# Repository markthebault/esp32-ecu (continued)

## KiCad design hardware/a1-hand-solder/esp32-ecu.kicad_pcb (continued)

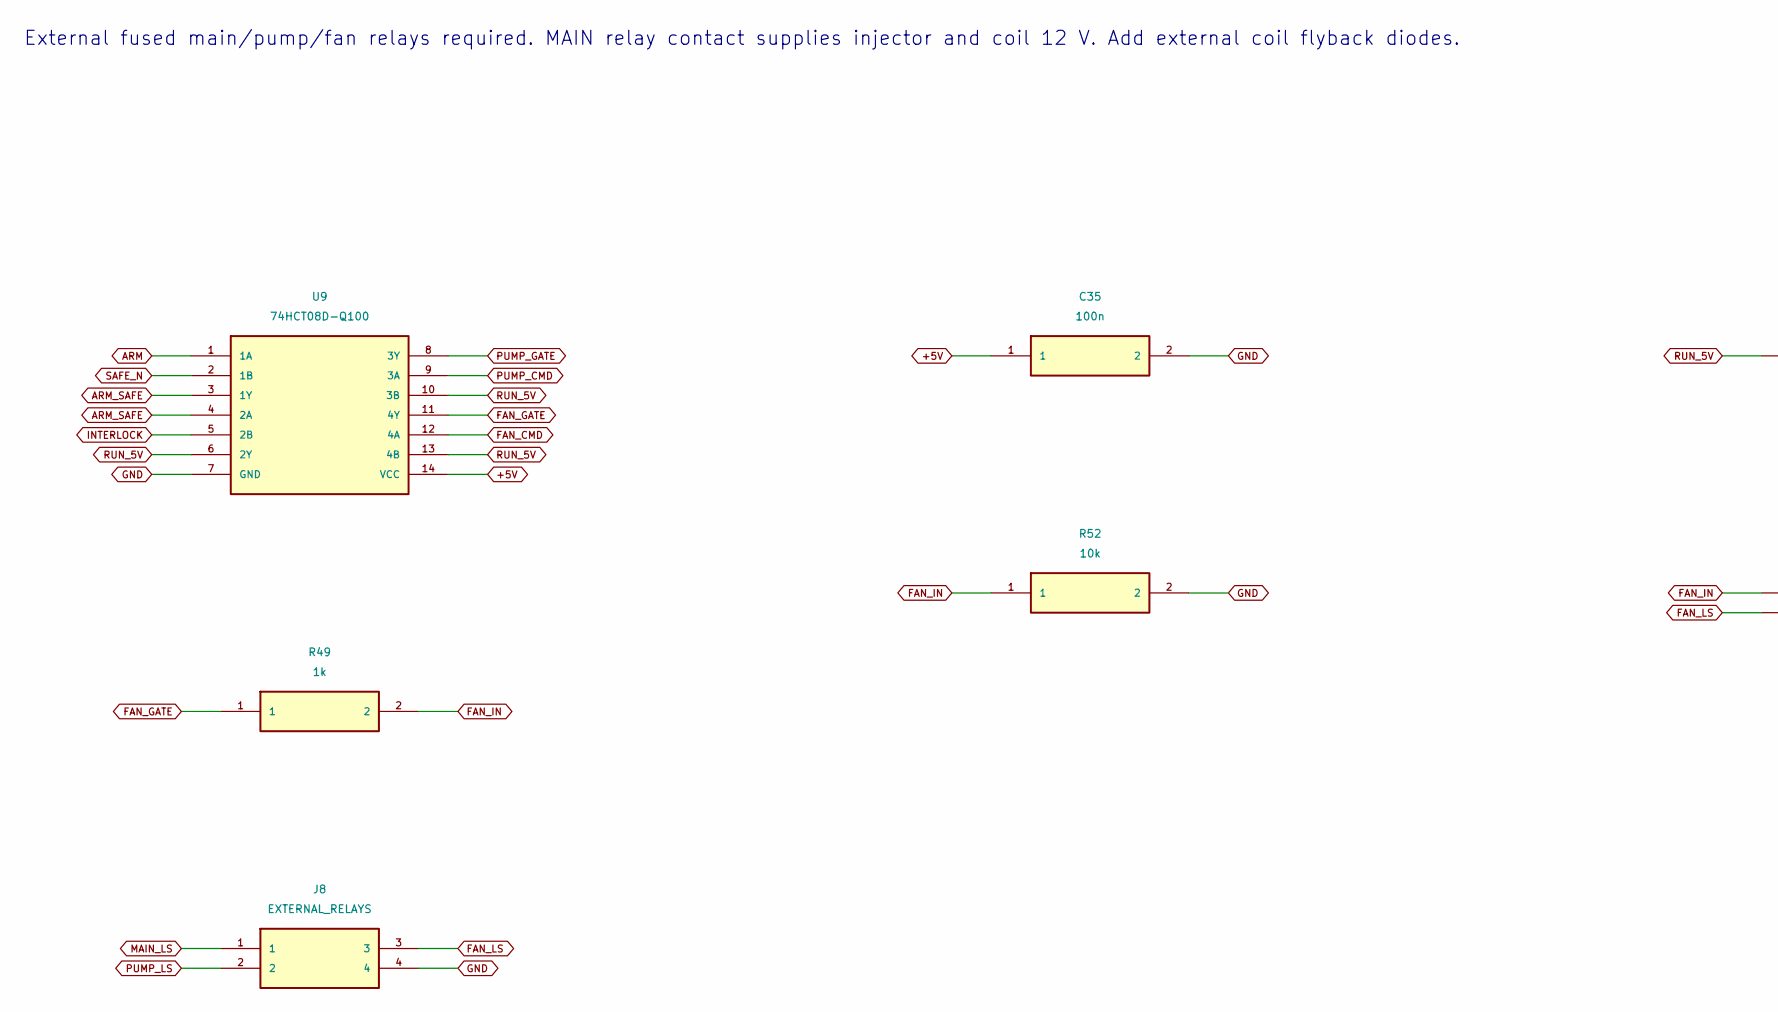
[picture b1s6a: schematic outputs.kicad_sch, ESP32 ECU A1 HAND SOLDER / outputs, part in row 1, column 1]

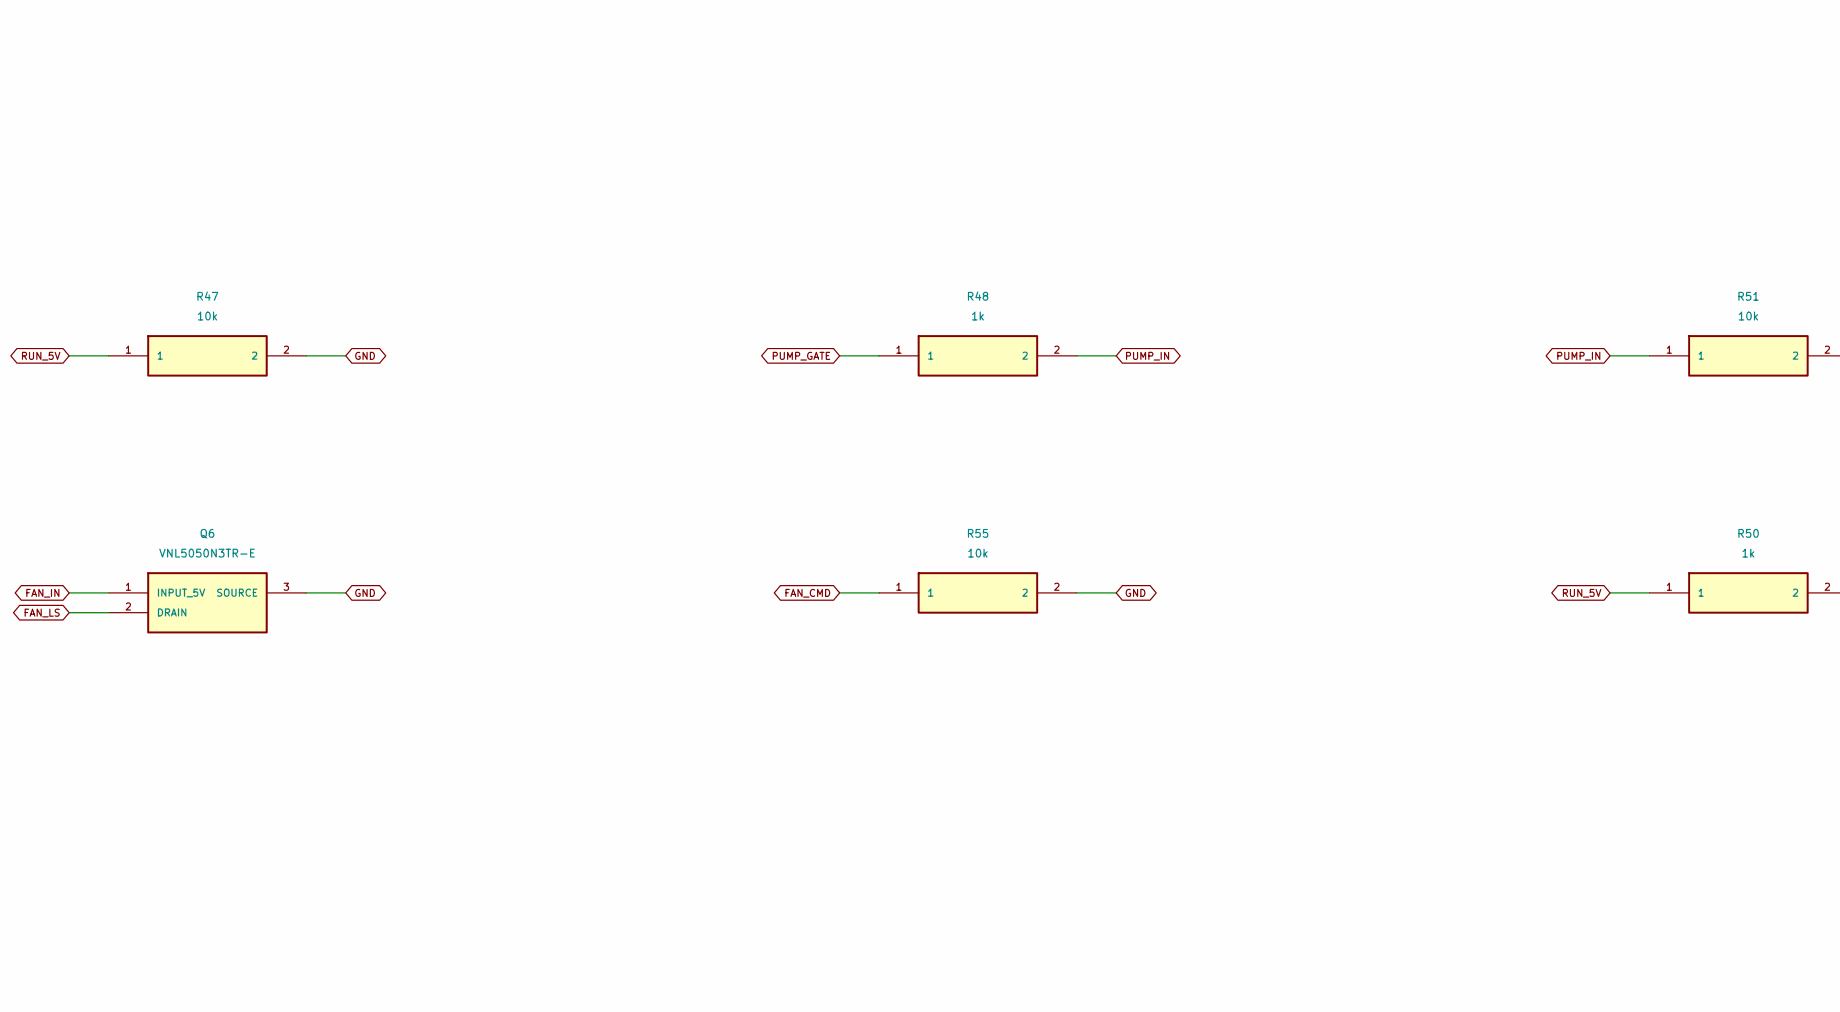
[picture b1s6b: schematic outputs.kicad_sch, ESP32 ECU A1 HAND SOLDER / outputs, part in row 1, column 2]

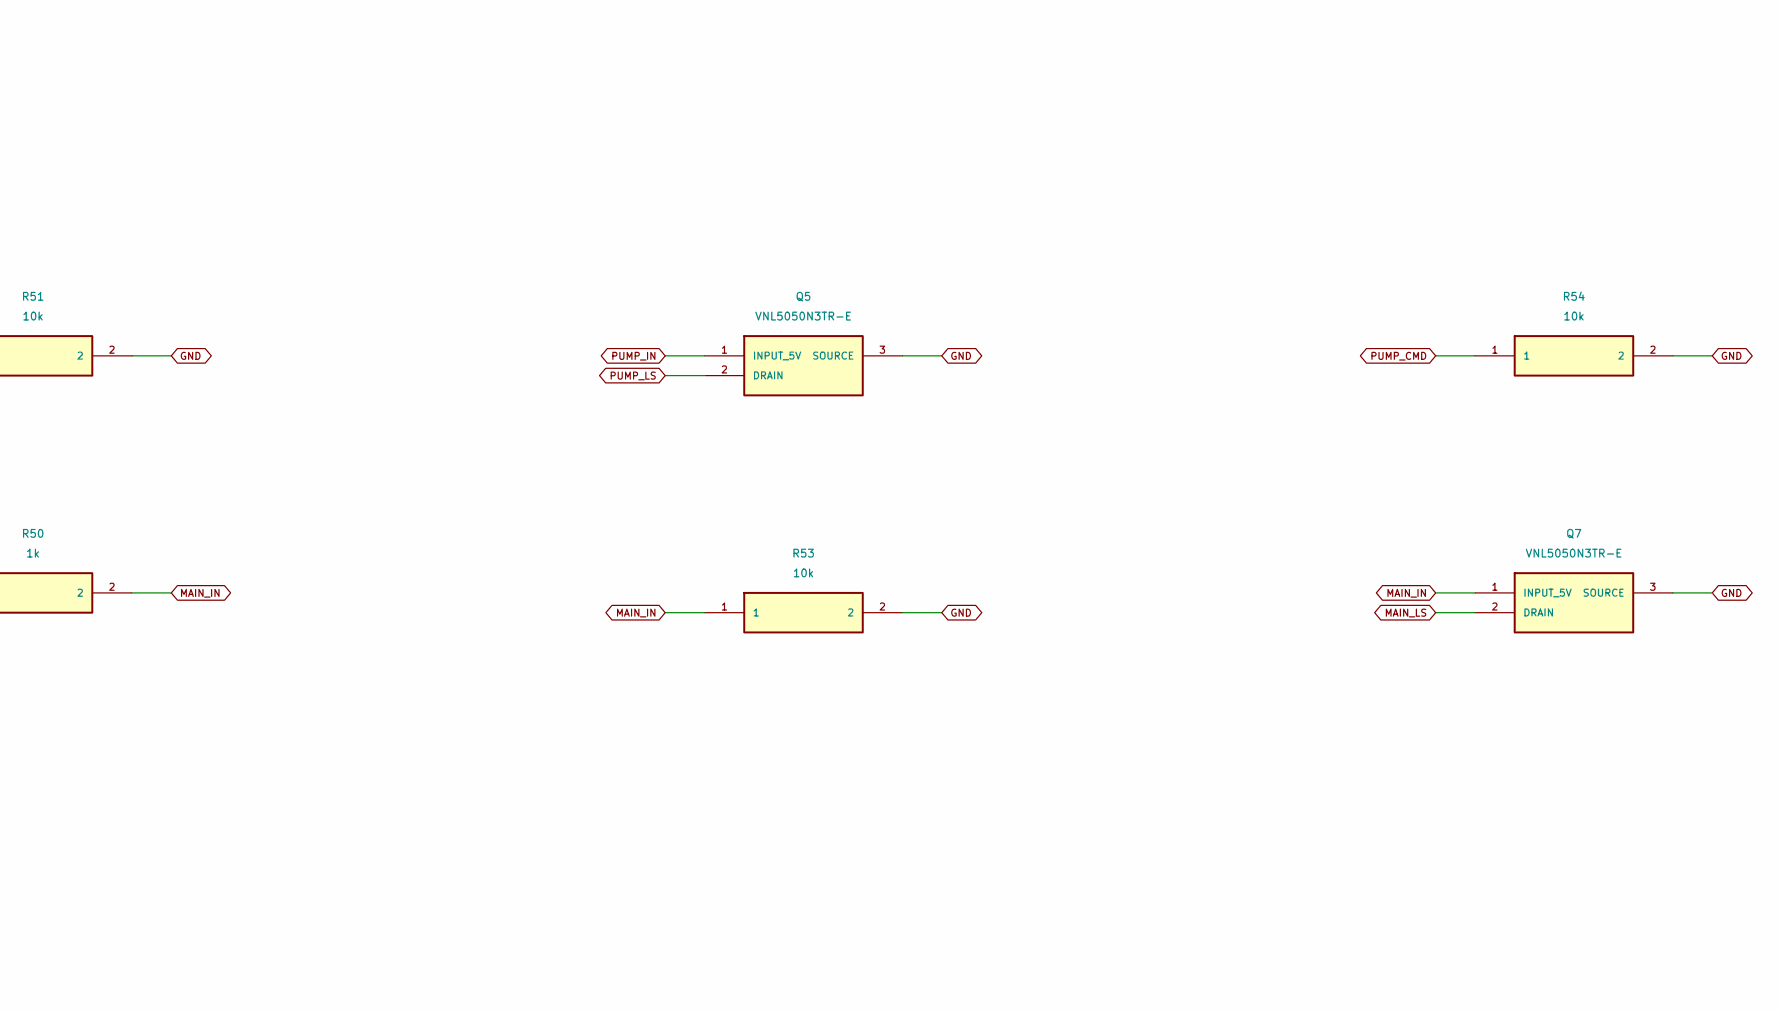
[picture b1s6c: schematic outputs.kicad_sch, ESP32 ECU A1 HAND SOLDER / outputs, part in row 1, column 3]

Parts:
C35: 100n; C_1206_3216Metric_Pad1.33x1.80mm_HandSolder
J8: EXTERNAL_RELAYS; JST_VH_B4P-VH_1x04_P3.96mm_Vertical; MPN B4P-VH(LF)(SN)
Q5, Q6, Q7: VNL5050N3TR-E; SOT-223-3_TabPin2; MPN VNL5050N3TR-E
R47, R51, R52, R53, R54, R55: 10k; R_1206_3216Metric_Pad1.30x1.75mm_HandSolder
R48, R49, R50: 1k; R_1206_3216Metric_Pad1.30x1.75mm_HandSolder
U9: 74HCT08D-Q100; SOIC-14_3.9x8.7mm_P1.27mm; MPN 74HCT08D-Q100,118

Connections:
+5V: C35.1, U9.14 (VCC); also elsewhere on the board
ARM: U9.1 (1A); also elsewhere on the board
ARM_SAFE: U9.3 (1Y), U9.4 (2A)
FAN_CMD: R55.1, U9.12 (4A); also elsewhere on the board
FAN_GATE: R49.1, U9.11 (4Y)
FAN_IN: Q6.1 (INPUT_5V), R49.2, R52.1
FAN_LS: J8.3, Q6.2 (DRAIN)
GND: C35.2, J8.4, Q5.3 (SOURCE), Q6.3 (SOURCE), Q7.3 (SOURCE), R47.2, R51.2, R52.2, R53.2, R54.2, R55.2, U9.7 (GND); also elsewhere on the board
INTERLOCK: U9.5 (2B); also elsewhere on the board
MAIN_IN: Q7.1 (INPUT_5V), R50.2, R53.1
MAIN_LS: J8.1, Q7.2 (DRAIN)
PUMP_CMD: R54.1, U9.9 (3A); also elsewhere on the board
PUMP_GATE: R48.1, U9.8 (3Y)
PUMP_IN: Q5.1 (INPUT_5V), R48.2, R51.1
PUMP_LS: J8.2, Q5.2 (DRAIN)
RUN_5V: R47.1, R50.1, U9.6 (2Y), U9.10 (3B), U9.13 (4B); also elsewhere on the board
SAFE_N: U9.2 (1B); also elsewhere on the board

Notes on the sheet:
External fused main/pump/fan relays required. MAIN relay contact supplies injector and coil 12 V. Add external coil flyback diodes.

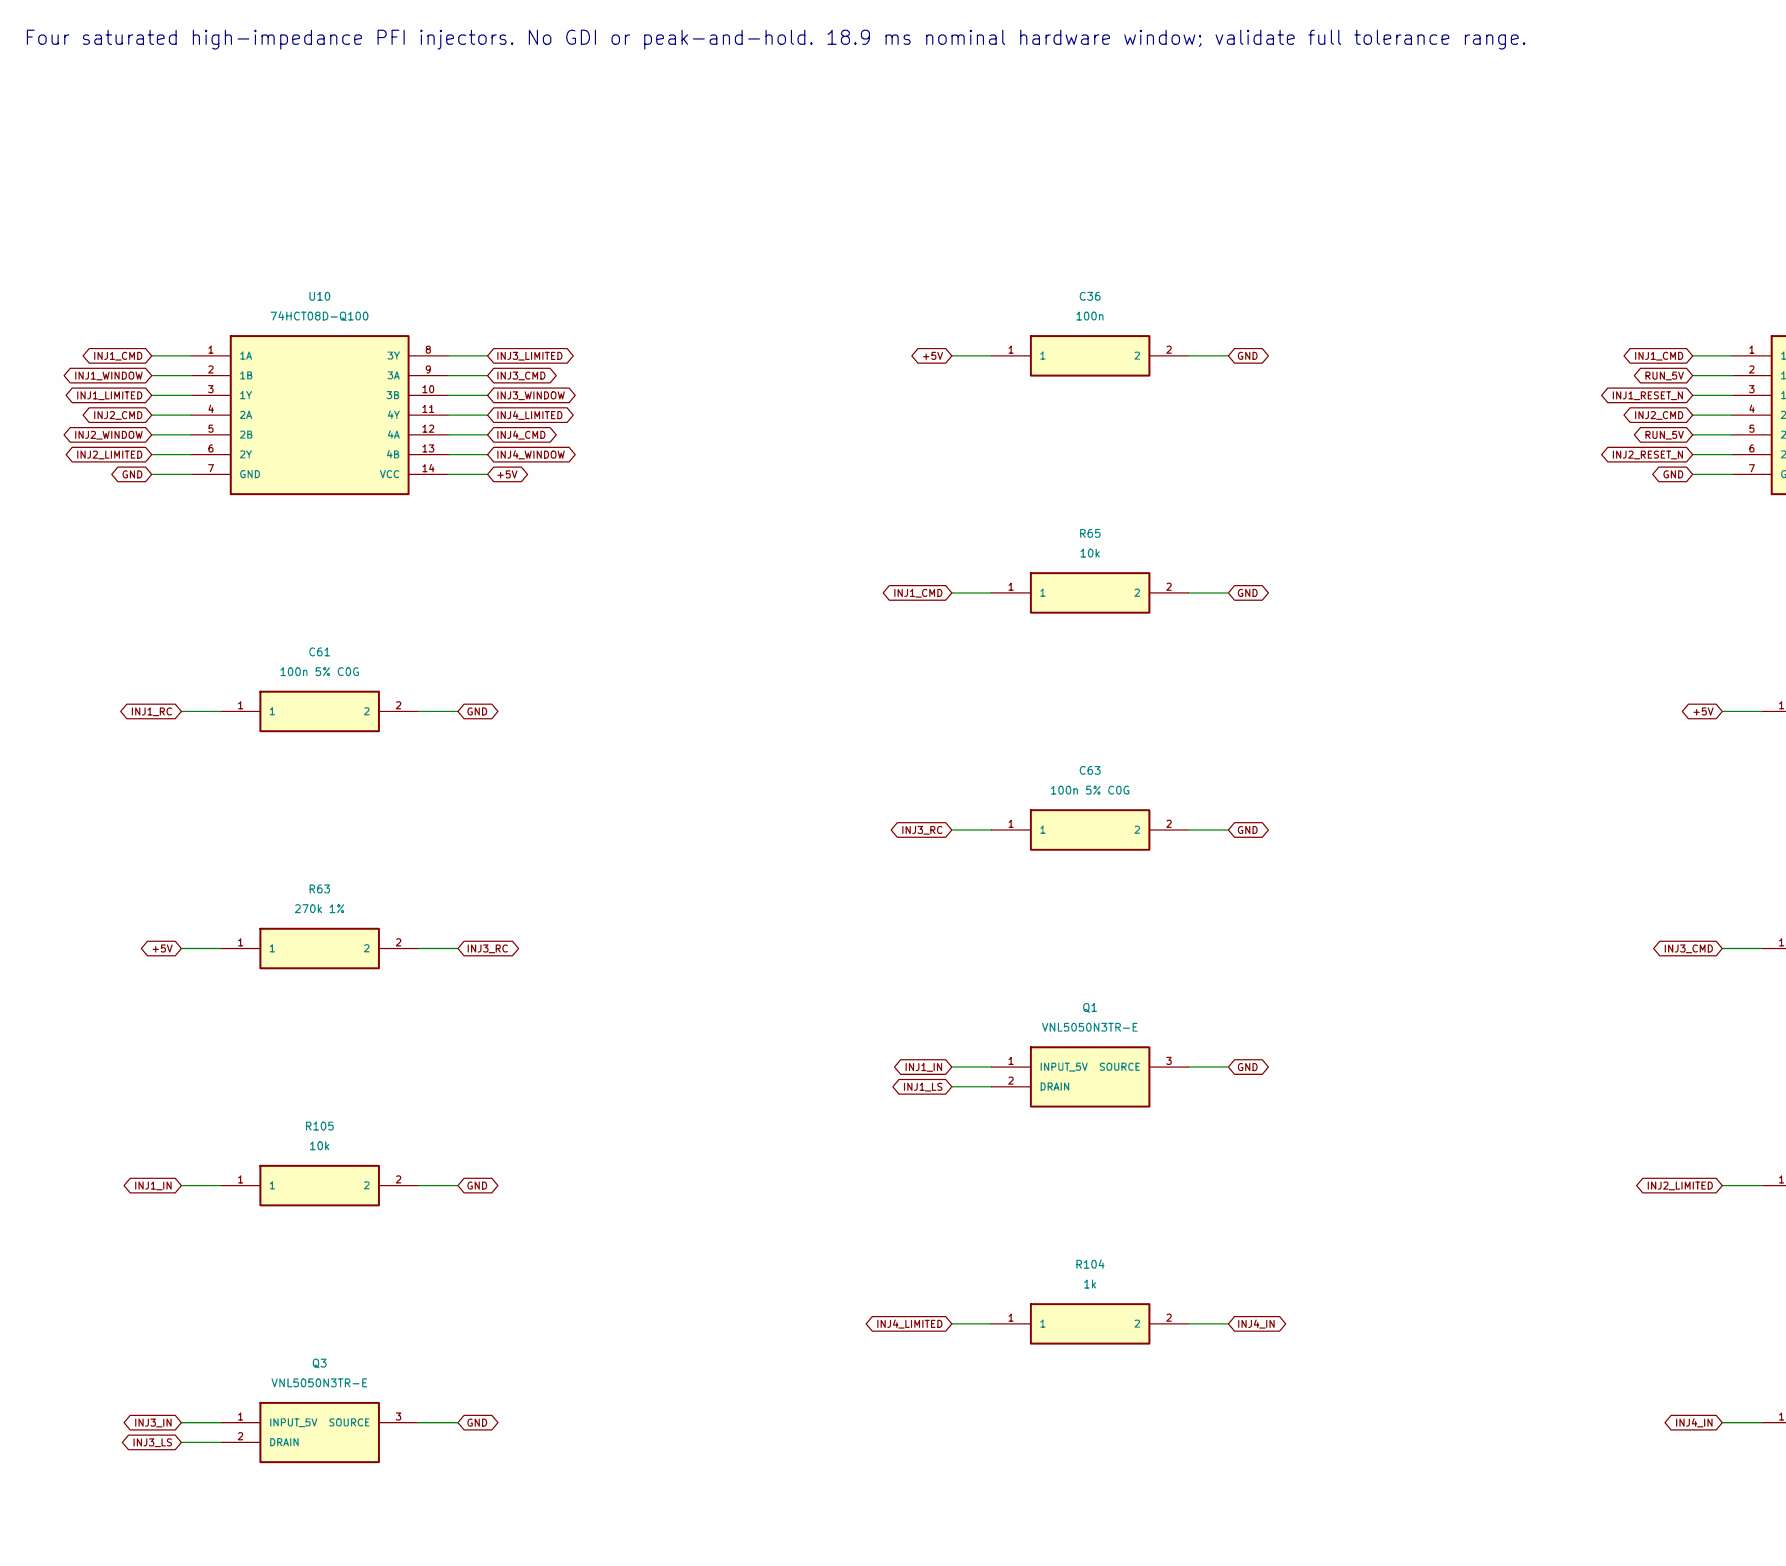
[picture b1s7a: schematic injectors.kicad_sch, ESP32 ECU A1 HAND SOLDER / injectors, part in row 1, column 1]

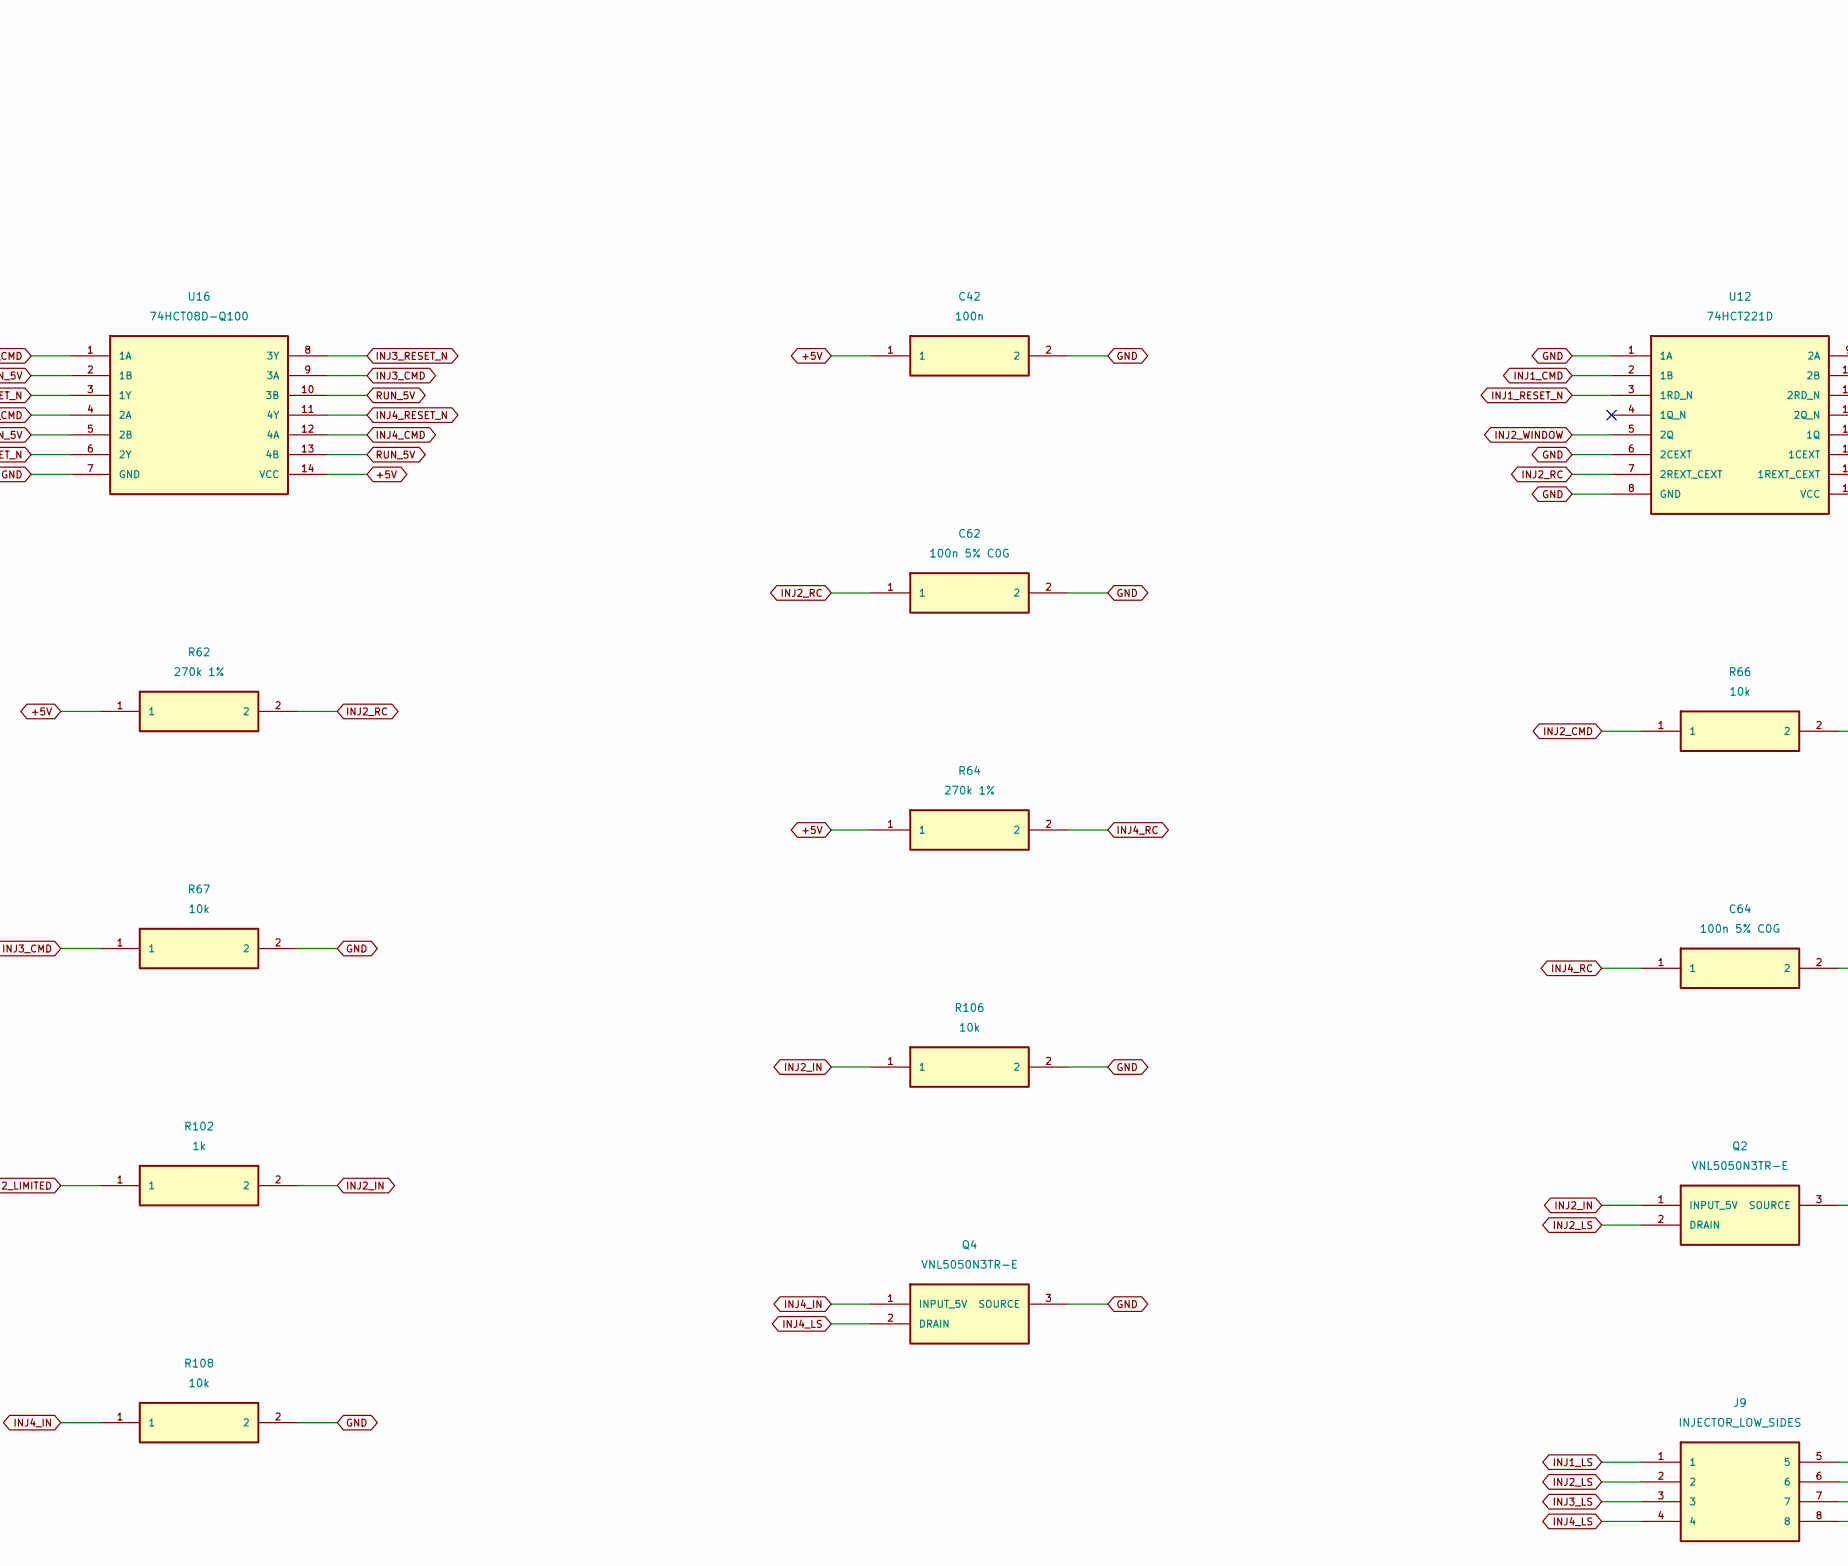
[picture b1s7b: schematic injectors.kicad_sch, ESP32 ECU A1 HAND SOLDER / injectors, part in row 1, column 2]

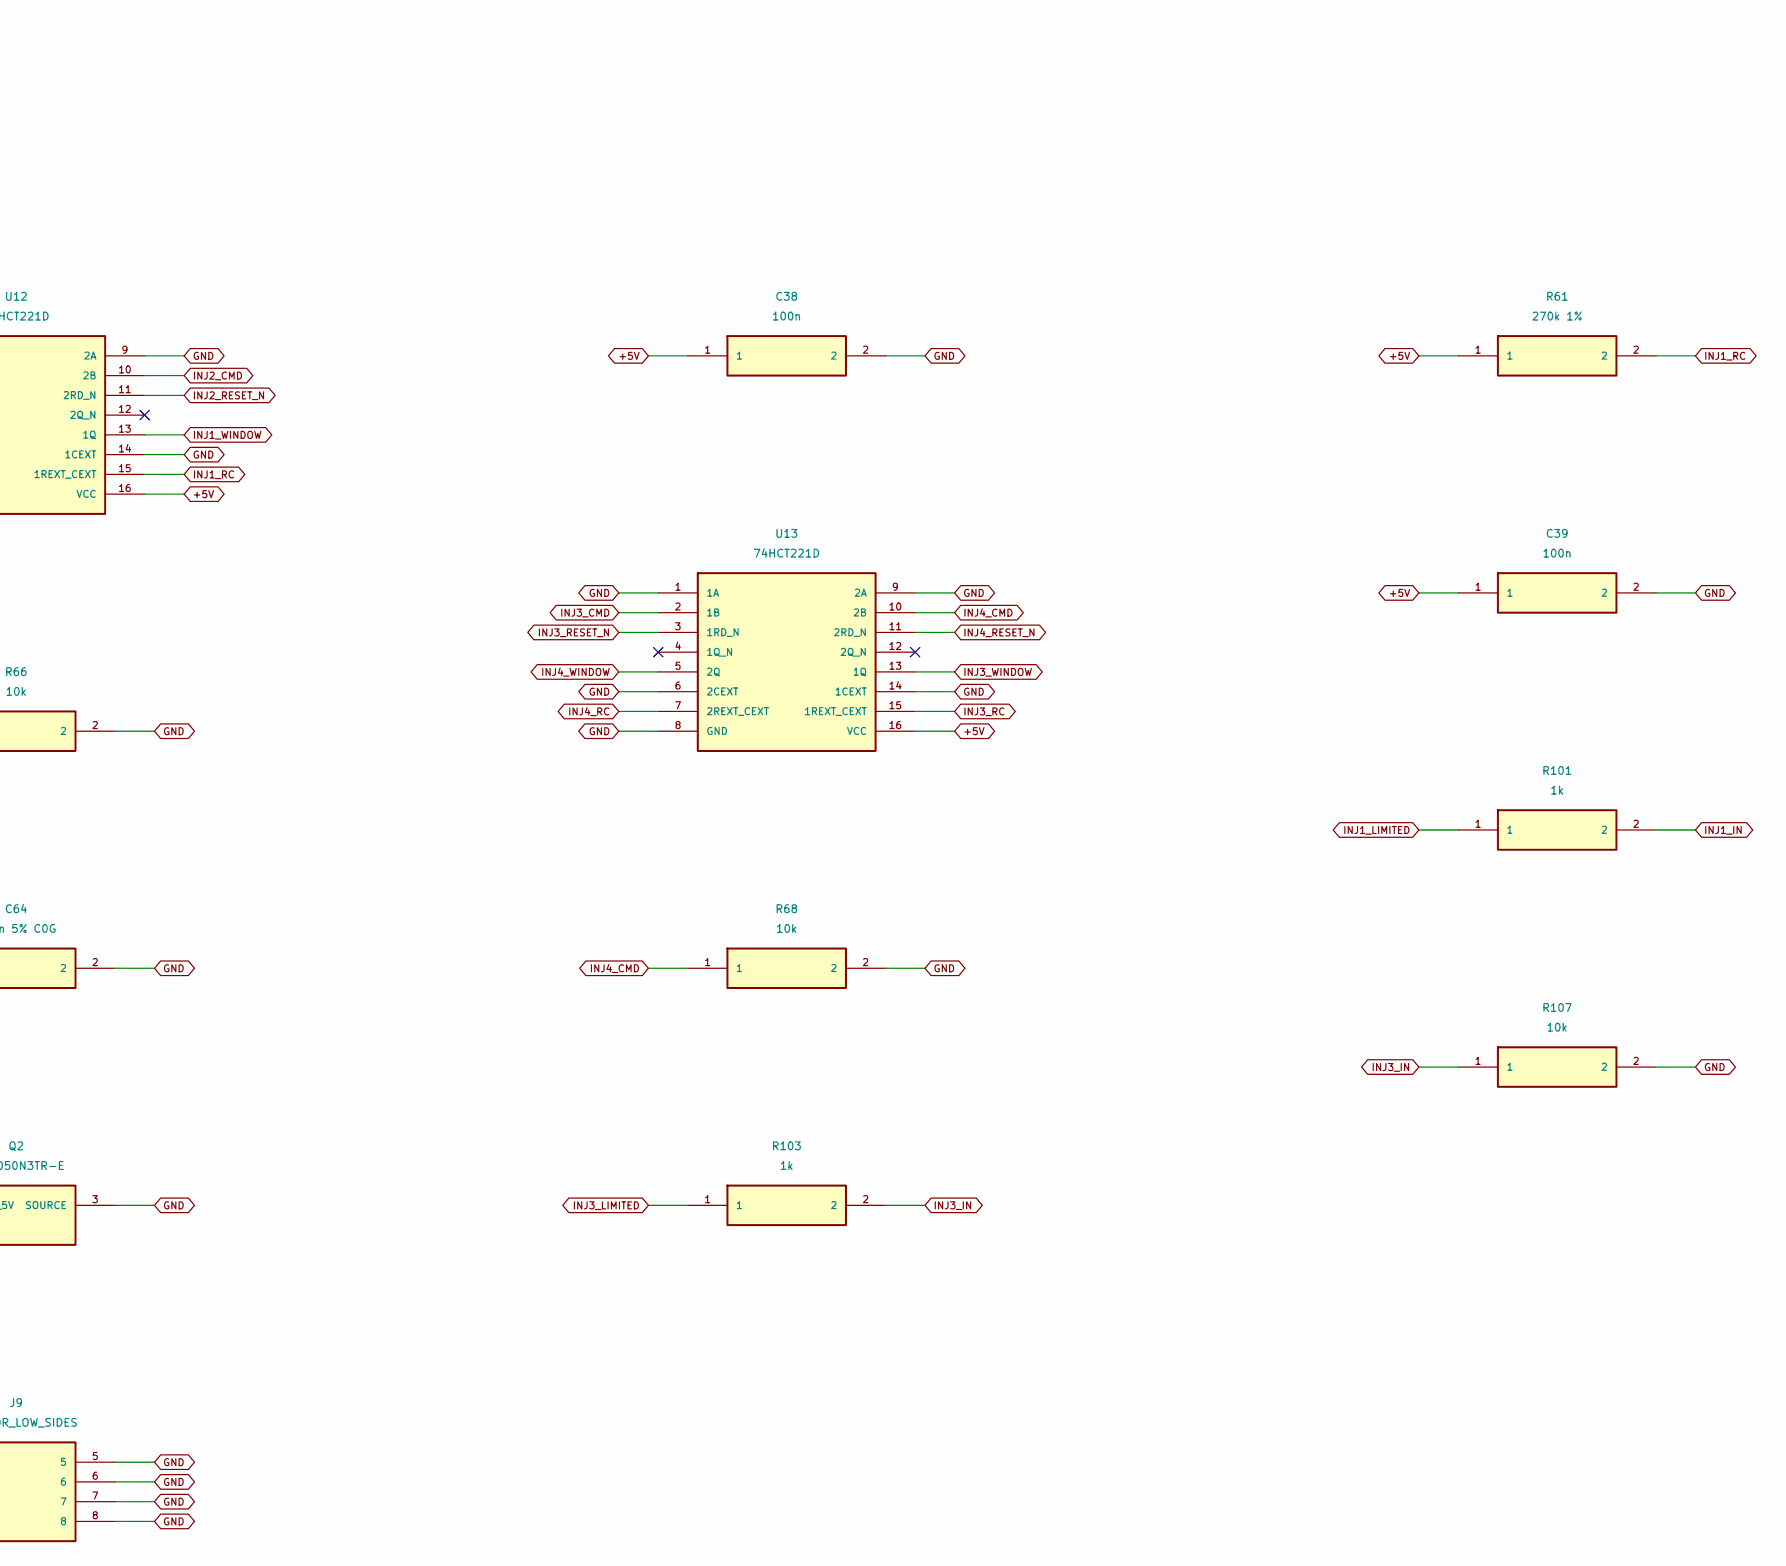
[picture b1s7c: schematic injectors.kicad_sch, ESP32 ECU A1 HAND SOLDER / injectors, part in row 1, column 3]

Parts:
C36, C38, C39, C42: 100n; C_1206_3216Metric_Pad1.33x1.80mm_HandSolder
C61, C62, C63, C64: 100n 5% C0G; C_1206_3216Metric_Pad1.33x1.80mm_HandSolder
J9: INJECTOR_LOW_SIDES; JST_VH_B8P-VH_1x08_P3.96mm_Vertical; MPN B8P-VH(LF)(SN)
Q1, Q2, Q3, Q4: VNL5050N3TR-E; SOT-223-3_TabPin2; MPN VNL5050N3TR-E
R61, R62, R63, R64: 270k 1%; R_1206_3216Metric_Pad1.30x1.75mm_HandSolder
R65, R66, R67, R68, R105, R106, R107, R108: 10k; R_1206_3216Metric_Pad1.30x1.75mm_HandSolder
R101, R102, R103, R104: 1k; R_1206_3216Metric_Pad1.30x1.75mm_HandSolder
U10, U16: 74HCT08D-Q100; SOIC-14_3.9x8.7mm_P1.27mm; MPN 74HCT08D-Q100,118
U12, U13: 74HCT221D; SOIC-16_3.9x9.9mm_P1.27mm; MPN 74HCT221D,118

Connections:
+5V: C36.1, C38.1, C39.1, C42.1, R61.1, R62.1, R63.1, R64.1, U10.14 (VCC), U12.16 (VCC), U13.16 (VCC), U16.14 (VCC); also elsewhere on the board
GND: C36.2, C38.2, C39.2, C42.2, C61.2, C62.2, C63.2, C64.2, J9.5, J9.6, J9.7, J9.8, Q1.3 (SOURCE), Q2.3 (SOURCE), Q3.3 (SOURCE), Q4.3 (SOURCE), R65.2, R66.2, R67.2, R68.2, R105.2, R106.2, R107.2, R108.2, U10.7 (GND), U12.1 (1A), U12.6 (2CEXT), U12.8 (GND), U12.9 (2A), U12.14 (1CEXT), U13.1 (1A), U13.6 (2CEXT), U13.8 (GND), U13.9 (2A), U13.14 (1CEXT), U16.7 (GND); also elsewhere on the board
INJ1_CMD: R65.1, U10.1 (1A), U12.2 (1B), U16.1 (1A); also elsewhere on the board
INJ1_IN: Q1.1 (INPUT_5V), R101.2, R105.1
INJ1_LIMITED: R101.1, U10.3 (1Y)
INJ1_LS: J9.1, Q1.2 (DRAIN)
INJ1_RC: C61.1, R61.2, U12.15 (1REXT_CEXT)
INJ1_RESET_N: U12.3 (1RD_N), U16.3 (1Y)
INJ1_WINDOW: U10.2 (1B), U12.13 (1Q)
INJ2_CMD: R66.1, U10.4 (2A), U12.10 (2B), U16.4 (2A); also elsewhere on the board
INJ2_IN: Q2.1 (INPUT_5V), R102.2, R106.1
INJ2_LIMITED: R102.1, U10.6 (2Y)
INJ2_LS: J9.2, Q2.2 (DRAIN)
INJ2_RC: C62.1, R62.2, U12.7 (2REXT_CEXT)
INJ2_RESET_N: U12.11 (2RD_N), U16.6 (2Y)
INJ2_WINDOW: U10.5 (2B), U12.5 (2Q)
INJ3_CMD: R67.1, U10.9 (3A), U13.2 (1B), U16.9 (3A); also elsewhere on the board
INJ3_IN: Q3.1 (INPUT_5V), R103.2, R107.1
INJ3_LIMITED: R103.1, U10.8 (3Y)
INJ3_LS: J9.3, Q3.2 (DRAIN)
INJ3_RC: C63.1, R63.2, U13.15 (1REXT_CEXT)
INJ3_RESET_N: U13.3 (1RD_N), U16.8 (3Y)
INJ3_WINDOW: U10.10 (3B), U13.13 (1Q)
INJ4_CMD: R68.1, U10.12 (4A), U13.10 (2B), U16.12 (4A); also elsewhere on the board
INJ4_IN: Q4.1 (INPUT_5V), R104.2, R108.1
INJ4_LIMITED: R104.1, U10.11 (4Y)
INJ4_LS: J9.4, Q4.2 (DRAIN)
INJ4_RC: C64.1, R64.2, U13.7 (2REXT_CEXT)
INJ4_RESET_N: U13.11 (2RD_N), U16.11 (4Y)
INJ4_WINDOW: U10.13 (4B), U13.5 (2Q)
RUN_5V: U16.2 (1B), U16.5 (2B), U16.10 (3B), U16.13 (4B); also elsewhere on the board

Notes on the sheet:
Four saturated high-impedance PFI injectors. No GDI or peak-and-hold. 18.9 ms nominal hardware window; validate full tolerance range.
